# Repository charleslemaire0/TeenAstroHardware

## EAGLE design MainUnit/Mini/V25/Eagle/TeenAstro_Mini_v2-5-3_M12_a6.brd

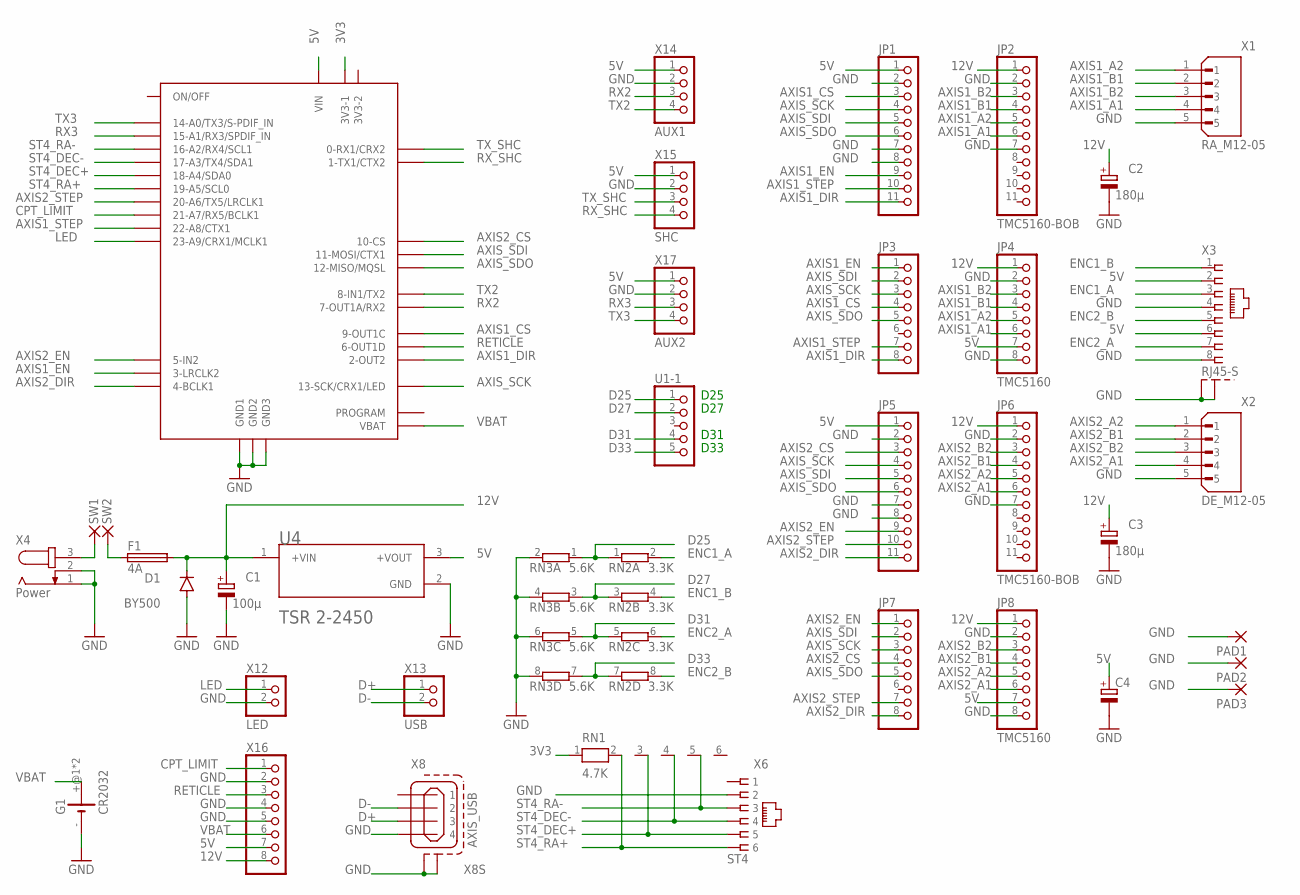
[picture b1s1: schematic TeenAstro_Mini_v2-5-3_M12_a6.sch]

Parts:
C1: 100µ; TAP5-80
C2, C3: 180µ; TAP5-80
C4: CPOL-EUTAP5-45; TAP5-45
D1: BY500; DO201-15
F1: 4A; SH22,5
G1: CR2032; BK-888
JP1, JP5: PINHD-1X11/LONG; 1X11
JP2, JP6: TMC5160-BOB; 1X11
JP3, JP7: PINHD-1X8/LONG; 1X08
JP4, JP8: TMC5160; 1X08
PAD1, PAD2, PAD3: 2,54/1,1
RN1: 4.7K; RN-6
RN2: 3.3K; SIL8
RN3: 5.6K; SIL8
SW1, SW2: 3,17/1,1
U1: TEENSY4.0; TEENSY40A
U1-1: PINHD-1X5/LONG; 1X05
U4: TSR_2-2450; TRACOPOWER_TSR_2-2450_0
X1: RA_M12-05; CONEC_43-01198_C
X2: DE_M12-05; CONEC_43-01198_C
X3: RJ45-S; RJ45-SHIELD
X4: Power; SPC4078
X6: ST4; RJ11-NO_SHIELD
X8: AXIS_USB; 85-32004-00X
X12: LED; 1X02
X13: USB; 1X02
X14: AUX1; 1X04
X15: SHC; 1X04
X16: PINHD-1X8/LONG; 1X08
X17: AUX2; 1X04

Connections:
3V3: RN1.1, U1.3V3-1
5V: C4.+, JP1.1, JP4.7, JP5.1, JP8.7, U1.VIN, U4.3 (+VOUT), X3.2, X3.6, X14.1, X15.1, X16.7, X17.1
12V: C1.+, C2.+, C3.+, D1.C, F1.2, JP2.1, JP4.1, JP6.1, JP8.1, U4.1 (+VIN), X16.8
AXIS1_A1: JP2.6, JP4.6, X1.4
AXIS1_A2: JP2.5, JP4.5, X1.1
AXIS1_B1: JP2.4, JP4.4, X1.2
AXIS1_B2: JP2.3, JP4.3, X1.3
AXIS1_CS: JP1.3, JP3.4, U1.9-OUT1C
AXIS1_DIR: JP1.11, JP3.8, U1.2-OUT2
AXIS1_EN: JP1.9, JP3.1, U1.3-LRCLK2
AXIS1_STEP: JP1.10, JP3.7, U1.22-A8/CTX1
AXIS2_A1: JP6.6, JP8.6, X2.4
AXIS2_A2: JP6.5, JP8.5, X2.1
AXIS2_B1: JP6.4, JP8.4, X2.2
AXIS2_B2: JP6.3, JP8.3, X2.3
AXIS2_CS: JP5.3, JP7.4, U1.10-CS/MQSR (10-CS)
AXIS2_DIR: JP5.11, JP7.8, U1.4-BCLK2 (4-BCLK1)
AXIS2_EN: JP5.9, JP7.1, U1.5-IN2
AXIS2_STEP: JP5.10, JP7.7, U1.20-A6/TX5/LRCLK1
AXIS_SCK: JP1.4, JP3.3, JP5.4, JP7.3, U1.13-SCK/CRX1/LED
AXIS_SDI: JP1.5, JP3.2, JP5.5, JP7.2, U1.11-MOSI/CTX1
AXIS_SDO: JP1.6, JP3.5, JP5.6, JP7.5, U1.12-MIO/MQSL (12-MISO/MQSL)
CPT_LIMIT: U1.21-A7/RX5/BCLK1, X16.1
D25: RN2.1, RN3.1, U1-1.1
D27: RN2.3 (1), RN3.3 (1), U1-1.2
D31: RN2.5 (1), RN3.5 (1), U1-1.4
D33: RN2.7 (1), RN3.7 (1), U1-1.5
D+: X8.3, X13.1
D-: X8.2, X13.2
ENC1_A: RN2.2, X3.3
ENC1_B: RN2.4 (2), X3.1
ENC2_A: RN2.6 (2), X3.7
ENC2_B: RN2.8 (2), X3.5
GND: C1.-, C2.-, C3.-, C4.-, D1.A, G1.-, JP1.2, JP1.7, JP1.8, JP2.2, JP2.7, JP4.2, JP4.8, JP5.2, JP5.7, JP5.8, JP6.2, JP6.7, JP8.2, JP8.8, PAD1.1, PAD2.1, PAD3.1, RN3.2, RN3.4 (2), RN3.6 (2), RN3.8 (2), U1.GND1, U1.GND2, U1.GND3, U4.2 (GND), X1.5, X2.5, X3.4, X3.8, X3.M1 (S1), X3.M2 (S2), X4.1, X4.2, X6.2, X8.4, X8.M1 (S1), X8.M2 (S2), X12.2, X14.2, X15.2, X16.2, X16.4, X16.5, X17.2
LED: U1.23-A9/CRX1/CCLK1 (23-A9/CRX1/MCLK1), X12.1
unnamed: SW1.1, X4.3
unnamed: F1.1, SW2.1
RETICLE: U1.6-OUT1D, X16.3
RX2: U1.7-RX2/OUT1A (7-OUT1A/RX2), X14.3
RX3: U1.15-A1/RX3/S-PDIF_IN (15-A1/RX3/SPDIF_IN), X17.3
RX_SHC: U1.1-TX1 (1-TX1/CTX2), X15.4
ST4_DEC+: RN1.3, U1.18-A4/SDA0, X6.5
ST4_DEC-: RN1.4, U1.17-A3/TX4/SDA1, X6.4
ST4_RA+: RN1.2, U1.19-A5/SCL0, X6.6
ST4_RA-: RN1.5, U1.16-A2/RX4/SCL1, X6.3
TX2: U1.8-TX2/IN1 (8-IN1/TX2), X14.4
TX3: U1.14-A0/TX3/S-PFI_OUT (14-A0/TX3/S-PDIF_IN), X17.4
TX_SHC: U1.0-RX1 (0-RX1/CRX2), X15.3
VBAT: G1.+@1 (+), G1.+@2 (+), U1.VBAT, X16.6

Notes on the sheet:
D25
D27
D31
D33

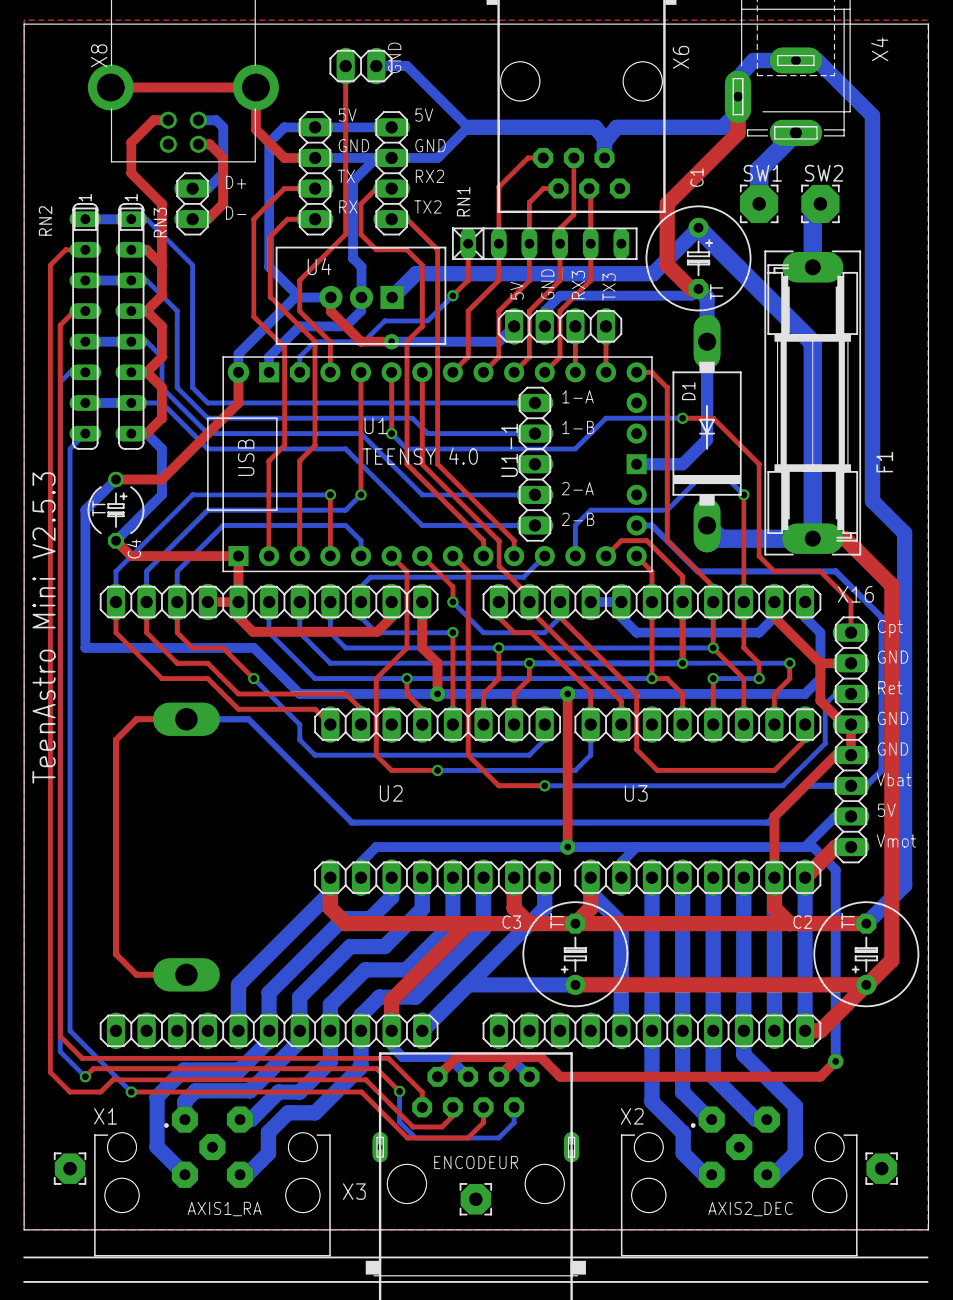
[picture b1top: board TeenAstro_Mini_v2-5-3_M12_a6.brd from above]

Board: 2 copper layers, 75.0 x 103.8 mm, 38 parts (1 on the bottom side), 49 nets.

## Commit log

2023-02-04 migrate Hardware definition
2023-03-05 add plexisglas panels
2023-03-05 fix a bug for the version 2.5.1
2023-04-01 Refactor storage
2023-04-01 add bottom part
2023-04-12 add version SHC 1.1
2023-04-24 add schema 2.5.2
2023-06-18 Add version 2.5.3
2023-06-26 Release SHC 1.2
2023-06-26 cosmetic change
2023-06-26 replace picture
2023-07-23 Release 2.5.4 mini Main Unit
2023-07-23 Add Model A Nema 17 cover
2023-07-23 Add Nema23 from thingiverse
2023-08-20 add alu case drawing for teenAstro focuser
2023-08-20 Add EAF motor drawing
2023-08-21 add Schaeffer front panel
2023-11-26 move fritzing geber file
2023-11-26 add eagle Version of the TeenAstro Mini
2024-01-28 update Tiny version from Jean David
2024-02-03 update tiny picture
2024-02-10 Add mechanical drawing
2024-02-11 add EQ6 kit
2024-02-11 add jpeg
2024-02-11 add jpg
